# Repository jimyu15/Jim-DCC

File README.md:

## Hardware

Schematics and layouts

Eagle PCB projects

#### Command Center

* DRV8801 enabled 2.8A driving ability with current sensing and protection
* 24-ch occupancy sensing ability
* 8-ch turnout servo control

#### Motor Decoder

* MSP430G2452 16MHz 8-bit MCU
* 24LC02 256Byte EEPROM
* DRV8838 enabled 1.8A driving ability with error protection
* Compatible with KATO DCC ready product

#### Headlight / Taillight Decoder

* MSP430G2452 16MHz 8-bit MCU
* 24LC02 256Byte EEPROM
* 2N7002DW enabled 2-ch 100mA LED driving
* Compatible with KATO DCC ready product

#### Indoor Light Decoder

* MSP430G2452 16MHz 8-bit MCU
* 24LC02 256Byte EEPROM
* 2N7002PW enabled 100mA LED driving

## CV_Writer

A simple tool to write all CVs to decoders.

Energia MSP430 project

## Decoder

Decoder which supports 128 step PWM motor control and general functions

Energia MSP430 project

## DCCpp_UNO

Modified DCC++ command station with occupancy sensing and servo control

Arduino Mega2560 project

Derived from DCC++

https://github.com/DccPlusPlus

## Servo

8-Ch servo control for turnouts

Energia MSP430 project

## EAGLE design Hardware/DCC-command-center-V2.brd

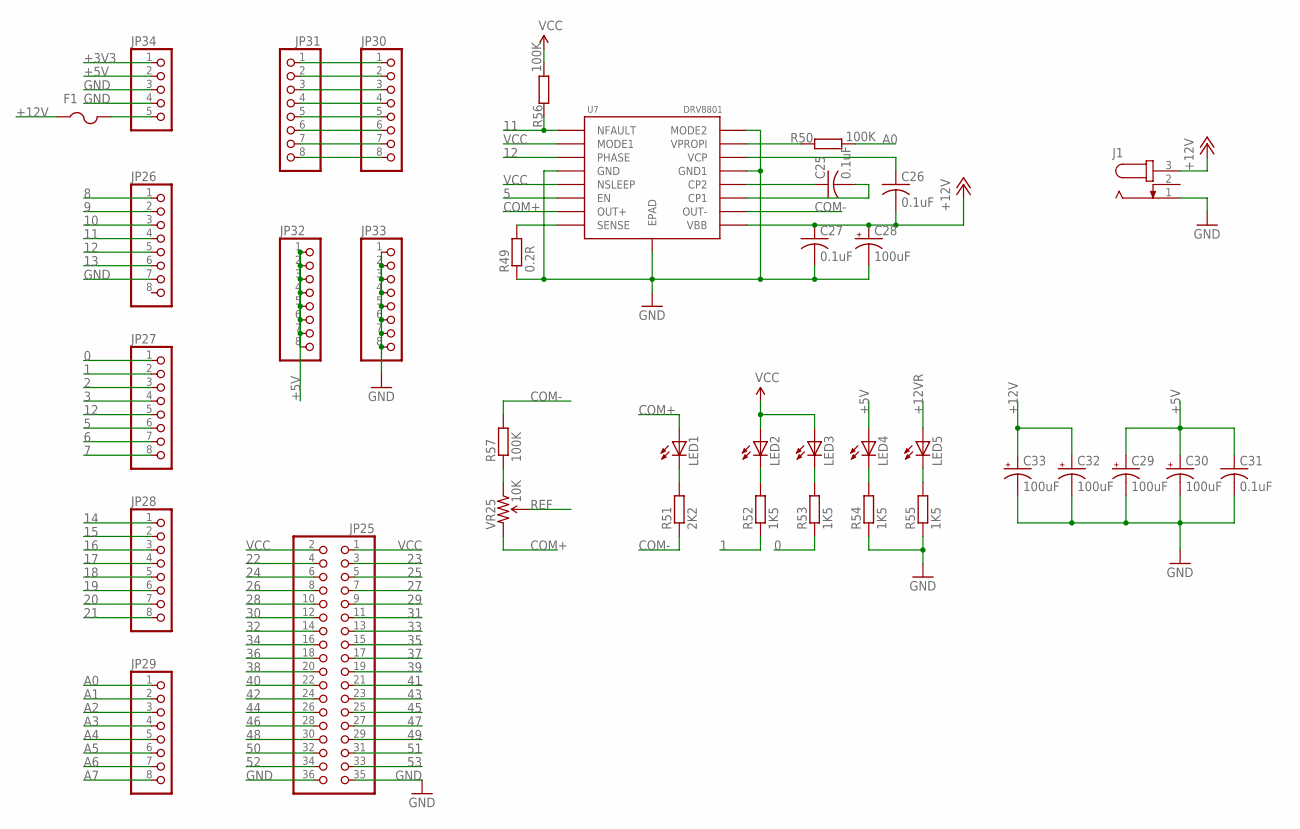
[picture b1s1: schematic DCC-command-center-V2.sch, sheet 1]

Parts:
C25, C26, C27, C31: 0.1uF; C0603
C28, C29, C30, C32, C33: 100uF; 153CLV-0505
F1: PTCFUSE-1812; 1812
J1: RAPC7120; RAPC712
JP25: PINHD-2X18_2.54; 2X18
JP26, JP27, JP28, JP29, JP30, JP31, JP32, JP33: PINHD-1X08_2.54-S; 1X08-S
JP34: PINHD-1X05_2.54-S; 1X05-S
LED1, LED2, LED3, LED4, LED5: LEDCHIP-LED0603; CHIP-LED0603
R49: 0.2R; R2512
R50, R56, R57: 100K; R0603
R51: 2K2; R0603
R52, R53, R54, R55: 1K5; R0603
U7: DRV8801; HTSSOP16
VR25: 10K; TRIMPOT-3MM-2

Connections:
0: JP27.1, R53.1
1: JP27.2, R52.1
2: JP27.3
3: JP27.4
5: JP27.6, U7.P$6 (EN)
6: JP27.7
7: JP27.8
8: JP26.1
9: JP26.2
10: JP26.3
11: JP26.4, R56.2, U7.P$1 (NFAULT)
12: JP26.5, JP27.5, U7.P$3 (PHASE)
13: JP26.6
14: JP28.1
15: JP28.2
16: JP28.3
17: JP28.4
18: JP28.5
19: JP28.6
20: JP28.7
21: JP28.8
22: JP25.4; also elsewhere on the board
23: JP25.3; also elsewhere on the board
24: JP25.6; also elsewhere on the board
25: JP25.5; also elsewhere on the board
26: JP25.8; also elsewhere on the board
27: JP25.7; also elsewhere on the board
28: JP25.10; also elsewhere on the board
29: JP25.9; also elsewhere on the board
30: JP25.12; also elsewhere on the board
31: JP25.11; also elsewhere on the board
32: JP25.14; also elsewhere on the board
33: JP25.13; also elsewhere on the board
34: JP25.16; also elsewhere on the board
35: JP25.15; also elsewhere on the board
36: JP25.18; also elsewhere on the board
37: JP25.17; also elsewhere on the board
38: JP25.20; also elsewhere on the board
39: JP25.19; also elsewhere on the board
40: JP25.22; also elsewhere on the board
41: JP25.21; also elsewhere on the board
42: JP25.24; also elsewhere on the board
43: JP25.23; also elsewhere on the board
44: JP25.26; also elsewhere on the board
45: JP25.25; also elsewhere on the board
46: JP25.28
47: JP25.27
48: JP25.30
49: JP25.29
50: JP25.32
51: JP25.31
52: JP25.34
53: JP25.33
+3V3: JP34.1
+5V: C29.+, C30.+, C31.1, JP32.1, JP32.2, JP32.3, JP32.4, JP32.5, JP32.6, JP32.7, JP32.8, JP34.2, LED4.A
+12V: C26.2, C27.1, C28.+, C32.+, C33.+, F1.1, J1.3, U7.P$9 (VBB)
+12VR: F1.2, JP34.5, LED5.A
A0: JP29.1, R50.1
A1: JP29.2
A2: JP29.3
A3: JP29.4
A4: JP29.5
A5: JP29.6
A6: JP29.7
A7: JP29.8
COM+: LED1.A, U7.P$7 (OUT+), VR25.3 (CW); also elsewhere on the board
COM-: R51.1, R57.2, U7.P$10 (OUT-); also elsewhere on the board
GND: C27.2, C28.-, C29.-, C30.-, C31.2, C32.-, C33.-, J1.1, JP25.35, JP25.36, JP26.7, JP33.1, JP33.2, JP33.3, JP33.4, JP33.5, JP33.6, JP33.7, JP33.8, JP34.3, JP34.4, R49.1, R54.1, R55.1, U7.P$4 (GND), U7.P$13 (GND1), U7.P$16 (MODE2), U7.P$17 (EPAD); also elsewhere on the board
unnamed: JP30.1, JP31.1
unnamed: JP30.2, JP31.2
unnamed: JP30.3, JP31.3
unnamed: JP30.4, JP31.4
unnamed: JP30.5, JP31.5
unnamed: JP30.6, JP31.6
unnamed: JP30.7, JP31.7
unnamed: JP30.8, JP31.8
unnamed: R49.2, U7.P$8 (SENSE)
unnamed: C25.1, U7.P$12 (CP2)
unnamed: C25.2, U7.P$11 (CP1)
unnamed: C26.1, U7.P$14 (VCP)
unnamed: R57.1, VR25.1 (CCW)
unnamed: R50.2, U7.P$15 (VPROPI)
unnamed: LED1.C, R51.2
unnamed: LED2.C, R52.2
unnamed: LED3.C, R53.2
unnamed: LED4.C, R54.2
unnamed: LED5.C, R55.2
REF: VR25.2 (WIPER); also elsewhere on the board
VCC: JP25.1, JP25.2, LED2.A, LED3.A, R56.1, U7.P$2 (MODE1), U7.P$5 (NSLEEP); also elsewhere on the board

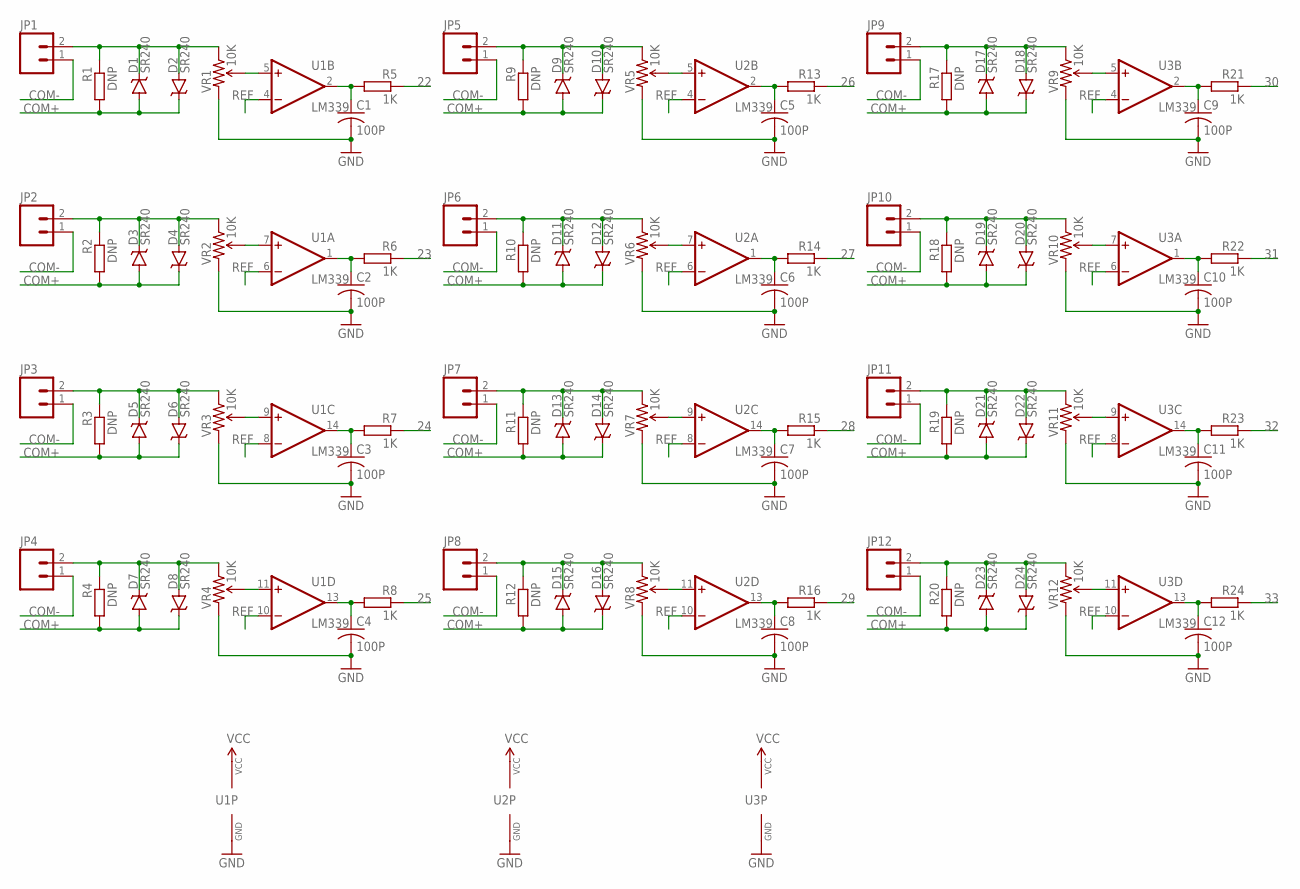
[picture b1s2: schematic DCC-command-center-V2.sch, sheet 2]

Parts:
C1, C2, C3, C4, C5, C6, C7, C8, C9, C10, C11, C12: 100P; C0603
D1, D2, D3, D4, D5, D6, D7, D8, D9, D10, D11, D12, D13, D14, D15, D16, D17, D18, D19, D20, D21, D22, D23, D24: SR240; SMA-DIODE
JP1, JP2, JP3, JP4, JP5, JP6, JP7, JP8, JP9, JP10, JP11, JP12: M02POGO_PIN_HOLES_ONLY; 1X02_PP_HOLES_ONLY
R1, R2, R3, R4, R9, R10, R11, R12, R17, R18, R19, R20: DNP; R0603
R5, R6, R7, R8, R13, R14, R15, R16, R21, R22, R23, R24: 1K; R0603
U1, U2, U3: LM339; TSSOP-14
VR1, VR2, VR3, VR4, VR5, VR6, VR7, VR8, VR9, VR10, VR11, VR12: 10K; TRIMPOT-3MM-2

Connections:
22: R5.1; also elsewhere on the board
23: R6.1; also elsewhere on the board
24: R7.1; also elsewhere on the board
25: R8.1; also elsewhere on the board
26: R13.1; also elsewhere on the board
27: R14.1; also elsewhere on the board
28: R15.1; also elsewhere on the board
29: R16.1; also elsewhere on the board
30: R21.1; also elsewhere on the board
31: R22.1; also elsewhere on the board
32: R23.1; also elsewhere on the board
33: R24.1; also elsewhere on the board
COM+: D1.A, D2.C, D3.A, D4.C, D5.A, D6.C, D7.A, D8.C, D9.A, D10.C, D11.A, D12.C, D13.A, D14.C, D15.A, D16.C, D17.A, D18.C, D19.A, D20.C, D21.A, D22.C, D23.A, D24.C, R1.2, R2.2, R3.2, R4.2, R9.2, R10.2, R11.2, R12.2, R17.2, R18.2, R19.2, R20.2; also elsewhere on the board
COM-: JP1.1, JP2.1, JP3.1, JP4.1, JP5.1, JP6.1, JP7.1, JP8.1, JP9.1, JP10.1, JP11.1, JP12.1; also elsewhere on the board
GND: C1.2, C2.2, C3.2, C4.2, C5.2, C6.2, C7.2, C8.2, C9.2, C10.2, C11.2, C12.2, U1.12 (GND), U2.12 (GND), U3.12 (GND), VR1.3 (CW), VR2.3 (CW), VR3.3 (CW), VR4.3 (CW), VR5.3 (CW), VR6.3 (CW), VR7.3 (CW), VR8.3 (CW), VR9.3 (CW), VR10.3 (CW), VR11.3 (CW), VR12.3 (CW); also elsewhere on the board
JP1: D1.C, D2.A, JP1.2, R1.1, VR1.1 (CCW)
JP2: D3.C, D4.A, JP2.2, R2.1, VR2.1 (CCW)
JP3: D5.C, D6.A, JP3.2, R3.1, VR3.1 (CCW)
JP4: D7.C, D8.A, JP4.2, R4.1, VR4.1 (CCW)
JP5: D9.C, D10.A, JP5.2, R9.1, VR5.1 (CCW)
JP6: D11.C, D12.A, JP6.2, R10.1, VR6.1 (CCW)
JP7: D13.C, D14.A, JP7.2, R11.1, VR7.1 (CCW)
JP8: D15.C, D16.A, JP8.2, R12.1, VR8.1 (CCW)
JP9: D17.C, D18.A, JP9.2, R17.1, VR9.1 (CCW)
JP10: D19.C, D20.A, JP10.2, R18.1, VR10.1 (CCW)
JP11: D21.C, D22.A, JP11.2, R19.1, VR11.1 (CCW)
JP12: D23.C, D24.A, JP12.2, R20.1, VR12.1 (CCW)
OP1: C1.1, R5.2, U1.2 (OUT)
OP2: C2.1, R6.2, U1.1 (OUT)
OP3: C3.1, R7.2, U1.14 (OUT)
OP4: C4.1, R8.2, U1.13 (OUT)
OP5: C5.1, R13.2, U2.2 (OUT)
OP6: C6.1, R14.2, U2.1 (OUT)
OP7: C7.1, R15.2, U2.14 (OUT)
OP8: C8.1, R16.2, U2.13 (OUT)
OP9: C9.1, R21.2, U3.2 (OUT)
OP10: C10.1, R22.2, U3.1 (OUT)
OP11: C11.1, R23.2, U3.14 (OUT)
OP12: C12.1, R24.2, U3.13 (OUT)
REF: U1.4 (-IN), U1.6 (-IN), U1.8 (-IN), U1.10 (-IN), U2.4 (-IN), U2.6 (-IN), U2.8 (-IN), U2.10 (-IN), U3.4 (-IN), U3.6 (-IN), U3.8 (-IN), U3.10 (-IN); also elsewhere on the board
VCC: U1.3 (VCC), U2.3 (VCC), U3.3 (VCC); also elsewhere on the board
VR1: U1.5 (+IN), VR1.2 (WIPER)
VR2: U1.7 (+IN), VR2.2 (WIPER)
VR3: U1.9 (+IN), VR3.2 (WIPER)
VR4: U1.11 (+IN), VR4.2 (WIPER)
VR5: U2.5 (+IN), VR5.2 (WIPER)
VR6: U2.7 (+IN), VR6.2 (WIPER)
VR7: U2.9 (+IN), VR7.2 (WIPER)
VR8: U2.11 (+IN), VR8.2 (WIPER)
VR9: U3.5 (+IN), VR9.2 (WIPER)
VR10: U3.7 (+IN), VR10.2 (WIPER)
VR11: U3.9 (+IN), VR11.2 (WIPER)
VR12: U3.11 (+IN), VR12.2 (WIPER)

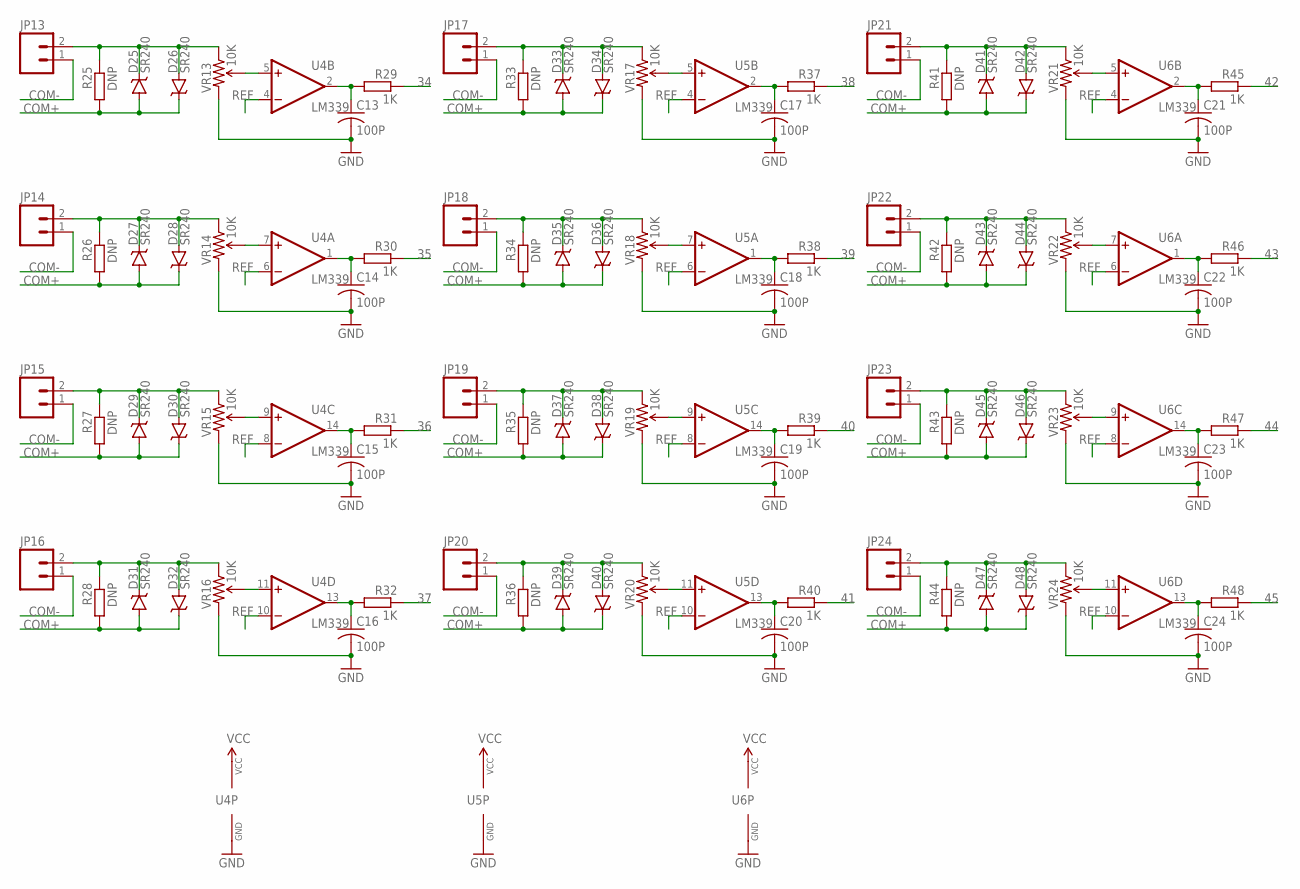
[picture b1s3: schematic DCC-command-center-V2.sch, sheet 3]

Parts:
C13, C14, C15, C16, C17, C18, C19, C20, C21, C22, C23, C24: 100P; C0603
D25, D26, D27, D28, D29, D30, D31, D32, D33, D34, D35, D36, D37, D38, D39, D40, D41, D42, D43, D44, D45, D46, D47, D48: SR240; SMA-DIODE
JP13, JP14, JP15, JP16, JP17, JP18, JP19, JP20, JP21, JP22, JP23, JP24: M02POGO_PIN_HOLES_ONLY; 1X02_PP_HOLES_ONLY
R25, R26, R27, R28, R33, R34, R35, R36, R41, R42, R43, R44: DNP; R0603
R29, R30, R31, R32, R37, R38, R39, R40, R45, R46, R47, R48: 1K; R0603
U4, U5, U6: LM339; TSSOP-14
VR13, VR14, VR15, VR16, VR17, VR18, VR19, VR20, VR21, VR22, VR23, VR24: 10K; TRIMPOT-3MM-2

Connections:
34: R29.1; also elsewhere on the board
35: R30.1; also elsewhere on the board
36: R31.1; also elsewhere on the board
37: R32.1; also elsewhere on the board
38: R37.1; also elsewhere on the board
39: R38.1; also elsewhere on the board
40: R39.1; also elsewhere on the board
41: R40.1; also elsewhere on the board
42: R45.1; also elsewhere on the board
43: R46.1; also elsewhere on the board
44: R47.1; also elsewhere on the board
45: R48.1; also elsewhere on the board
COM+: D25.A, D26.C, D27.A, D28.C, D29.A, D30.C, D31.A, D32.C, D33.A, D34.C, D35.A, D36.C, D37.A, D38.C, D39.A, D40.C, D41.A, D42.C, D43.A, D44.C, D45.A, D46.C, D47.A, D48.C, R25.2, R26.2, R27.2, R28.2, R33.2, R34.2, R35.2, R36.2, R41.2, R42.2, R43.2, R44.2; also elsewhere on the board
COM-: JP13.1, JP14.1, JP15.1, JP16.1, JP17.1, JP18.1, JP19.1, JP20.1, JP21.1, JP22.1, JP23.1, JP24.1; also elsewhere on the board
GND: C13.2, C14.2, C15.2, C16.2, C17.2, C18.2, C19.2, C20.2, C21.2, C22.2, C23.2, C24.2, U4.12 (GND), U5.12 (GND), U6.12 (GND), VR13.3 (CW), VR14.3 (CW), VR15.3 (CW), VR16.3 (CW), VR17.3 (CW), VR18.3 (CW), VR19.3 (CW), VR20.3 (CW), VR21.3 (CW), VR22.3 (CW), VR23.3 (CW), VR24.3 (CW); also elsewhere on the board
JP13: D25.C, D26.A, JP13.2, R25.1, VR13.1 (CCW)
JP14: D27.C, D28.A, JP14.2, R26.1, VR14.1 (CCW)
JP15: D29.C, D30.A, JP15.2, R27.1, VR15.1 (CCW)
JP16: D31.C, D32.A, JP16.2, R28.1, VR16.1 (CCW)
JP17: D33.C, D34.A, JP17.2, R33.1, VR17.1 (CCW)
JP18: D35.C, D36.A, JP18.2, R34.1, VR18.1 (CCW)
JP19: D37.C, D38.A, JP19.2, R35.1, VR19.1 (CCW)
JP20: D39.C, D40.A, JP20.2, R36.1, VR20.1 (CCW)
JP21: D41.C, D42.A, JP21.2, R41.1, VR21.1 (CCW)
JP22: D43.C, D44.A, JP22.2, R42.1, VR22.1 (CCW)
JP23: D45.C, D46.A, JP23.2, R43.1, VR23.1 (CCW)
JP24: D47.C, D48.A, JP24.2, R44.1, VR24.1 (CCW)
OP13: C13.1, R29.2, U4.2 (OUT)
OP14: C14.1, R30.2, U4.1 (OUT)
OP15: C15.1, R31.2, U4.14 (OUT)
OP16: C16.1, R32.2, U4.13 (OUT)
OP17: C17.1, R37.2, U5.2 (OUT)
OP18: C18.1, R38.2, U5.1 (OUT)
OP19: C19.1, R39.2, U5.14 (OUT)
OP20: C20.1, R40.2, U5.13 (OUT)
OP21: C21.1, R45.2, U6.2 (OUT)
OP22: C22.1, R46.2, U6.1 (OUT)
OP23: C23.1, R47.2, U6.14 (OUT)
OP24: C24.1, R48.2, U6.13 (OUT)
REF: U4.4 (-IN), U4.6 (-IN), U4.8 (-IN), U4.10 (-IN), U5.4 (-IN), U5.6 (-IN), U5.8 (-IN), U5.10 (-IN), U6.4 (-IN), U6.6 (-IN), U6.8 (-IN), U6.10 (-IN); also elsewhere on the board
VCC: U4.3 (VCC), U5.3 (VCC), U6.3 (VCC); also elsewhere on the board
VR13: U4.5 (+IN), VR13.2 (WIPER)
VR14: U4.7 (+IN), VR14.2 (WIPER)
VR15: U4.9 (+IN), VR15.2 (WIPER)
VR16: U4.11 (+IN), VR16.2 (WIPER)
VR17: U5.5 (+IN), VR17.2 (WIPER)
VR18: U5.7 (+IN), VR18.2 (WIPER)
VR19: U5.9 (+IN), VR19.2 (WIPER)
VR20: U5.11 (+IN), VR20.2 (WIPER)
VR21: U6.5 (+IN), VR21.2 (WIPER)
VR22: U6.7 (+IN), VR22.2 (WIPER)
VR23: U6.9 (+IN), VR23.2 (WIPER)
VR24: U6.11 (+IN), VR24.2 (WIPER)

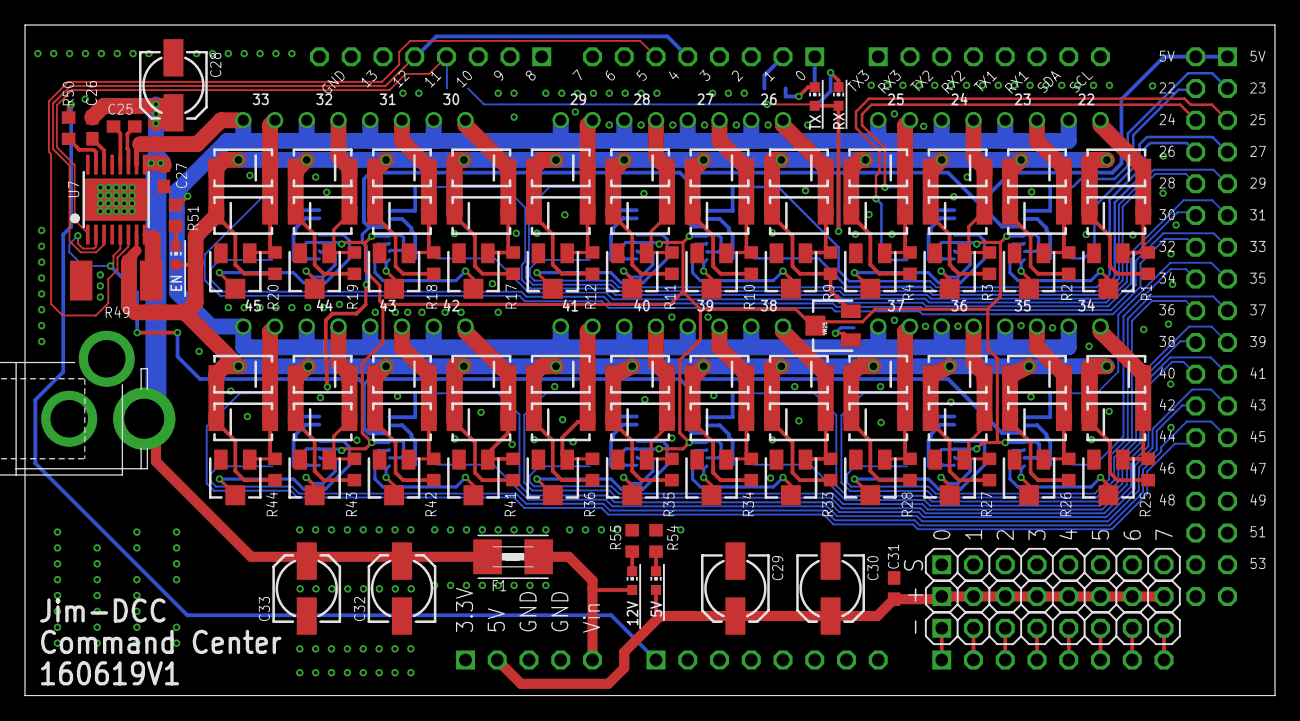
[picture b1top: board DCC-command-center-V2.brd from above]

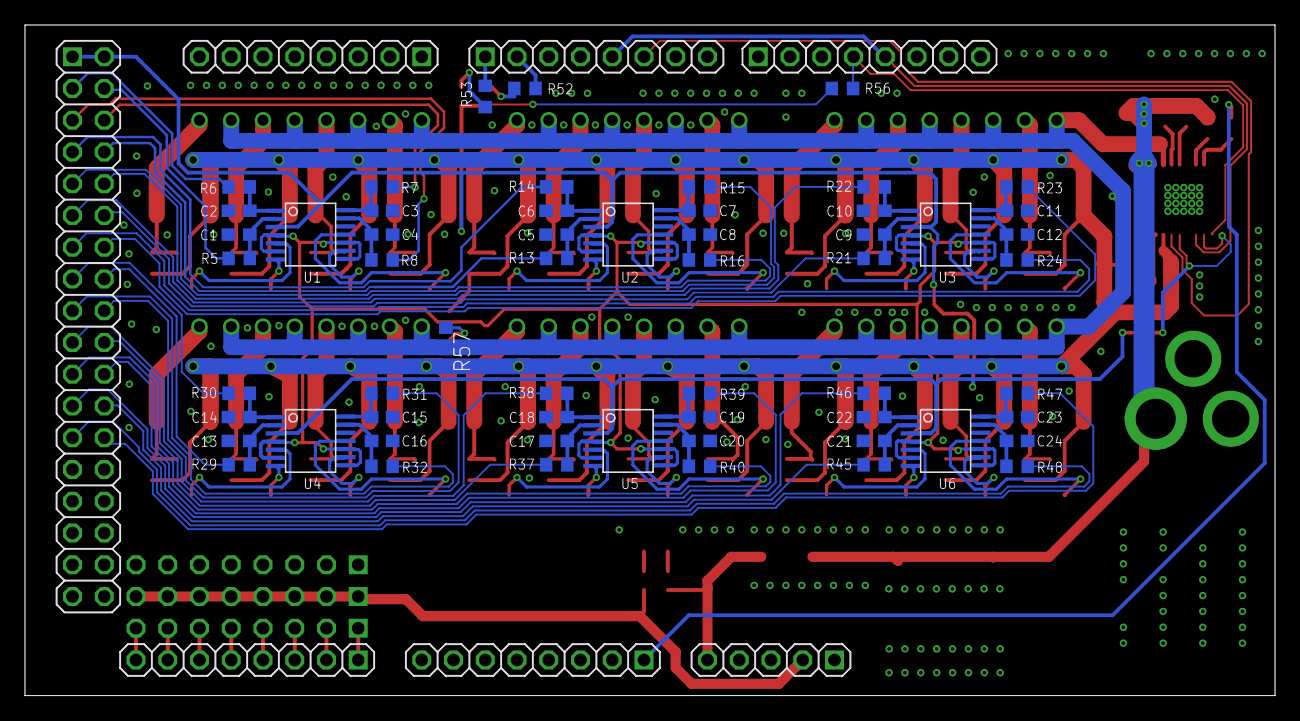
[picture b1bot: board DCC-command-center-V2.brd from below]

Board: 2 copper layers, 100.0 x 53.6 mm, 211 parts (66 on the bottom side), 129 nets.

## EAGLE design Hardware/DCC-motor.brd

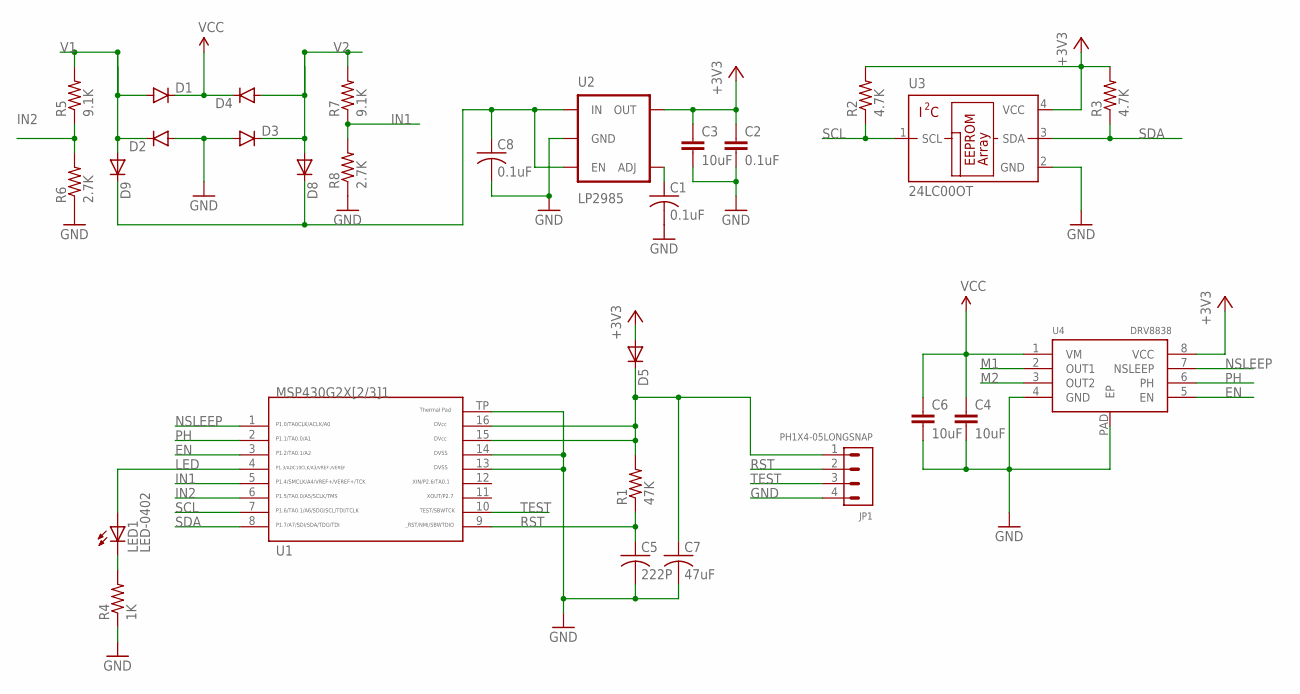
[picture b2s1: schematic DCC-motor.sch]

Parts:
C1, C8: 0.1uF; C0402
C2: 0.1uF; 0603-CAP
C3, C4, C6: 10uF; 0603-CAP
C5: 222P; C0402
C7: 47uF; C0402
D1, D2, D3, D4: DIODESOD123; SOD-123
D5, D8, D9: DIODE-SOD523; SOD523
JP1: PH1X4-05LONGSNAP; PHLS005-1-4
LED1: LED-0402; 0402-LED
R1: 47K; R0402
R2, R3: 4.7K; R0402
R4: 1K; R0402
R5, R7: 9.1K; R0402
R6, R8: 2.7K; R0402
U1: G2X[2/3]1---RSA16; RSA16
U2: LP2985; SOT23-5
U3: 24LC00OT; SOT23-5L
U4: DRV8838; WSON-8-PAD

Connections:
+3V3: C2.1, C3.1, D5.A, R2.2, R3.2, U2.5 (OUT), U3.4 (VCC), U4.8 (VCC)
EN: U1.3, U4.5 (EN)
GND: C1.2, C2.2, C3.2, C4.2, C5.2, C6.2, C7.2, C8.2, D2.A, D3.A, JP1.4, R4.1, R6.1, R8.1, U1.13, U1.14, U1.TP, U2.2 (GND), U3.2 (GND), U4.4 (GND), U4.PAD (EP)
IN1: R7.1, R8.2, U1.5
IN2: R5.1, R6.2, U1.6
LED: LED1.A, U1.4
M1: U4.2 (OUT1)
M2: U4.3 (OUT2)
unnamed: C1.1, U2.4 (ADJ)
unnamed: C8.1, D8.C, D9.C, U2.1 (IN), U2.3 (EN)
unnamed: LED1.C, R4.2
unnamed: C7.1, D5.C, JP1.1, R1.2, U1.15, U1.16
NSLEEP: U1.1, U4.7 (NSLEEP)
PH: U1.2, U4.6 (PH)
RST: C5.1, JP1.2, R1.1, U1.9
SCL: R2.1, U1.7, U3.1 (SCL)
SDA: R3.1, U1.8, U3.3 (SDA)
TEST: JP1.3, U1.10
V1: D1.A, D2.C, D9.A, R5.2
V2: D3.C, D4.A, D8.A, R7.2
VCC: C4.1, C6.1, D1.C, D4.C, U4.1 (VM)

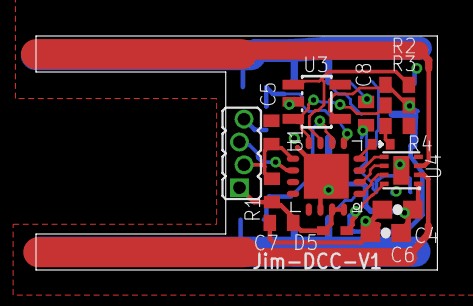
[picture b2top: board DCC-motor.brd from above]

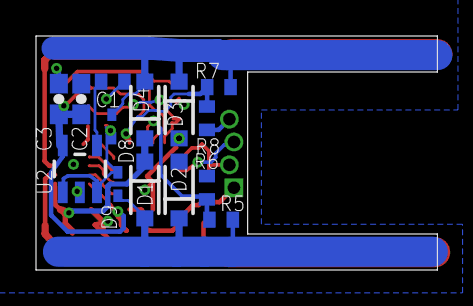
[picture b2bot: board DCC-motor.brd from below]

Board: 2 copper layers, 22.3 x 13.0 mm, 29 parts (14 on the bottom side), 19 nets.

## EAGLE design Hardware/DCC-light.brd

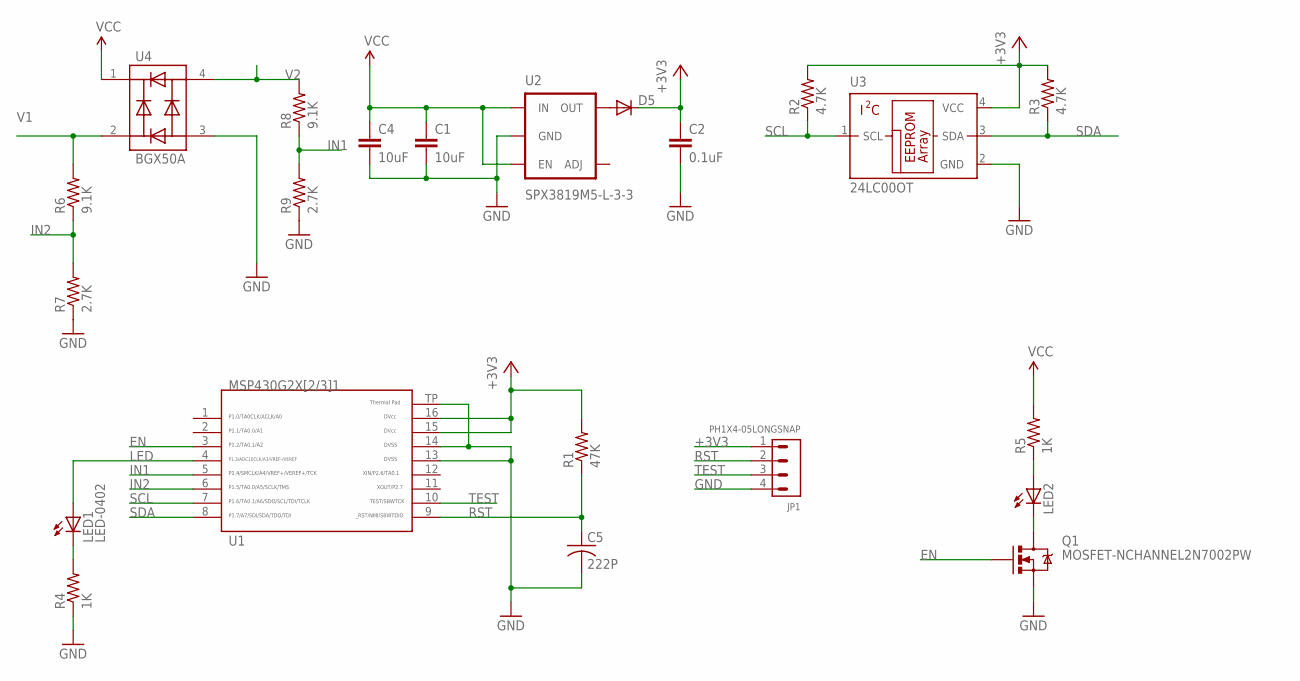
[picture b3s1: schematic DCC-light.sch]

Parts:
C1: 10uF; 0402-CAP
C2: 0.1uF; 0603-CAP
C4: 10uF; 0603-CAP
C5: 222P; C0402
D5: DIODE-SOD523; SOD523
JP1: PH1X4-05LONGSNAP; PHLS005-1-4
LED1: LED-0402; 0402-LED
LED2: LEDSMT1206; 1206
Q1: MOSFET-NCHANNEL2N7002PW; SOT323
R1: 47K; R0402
R2, R3: 4.7K; R0402
R4: 1K; R0402
R5: 1K; R0603
R6, R8: 9.1K; R0402
R7, R9: 2.7K; R0402
U1: G2X[2/3]1---RSA16; RSA16
U2: SPX3819M5-L-3-3; SOT23-5
U3: 24LC00OT; SOT23-5L
U4: BGX50A; SOT143

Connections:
+3V3: C2.1, D5.C, JP1.1, R1.2, R2.2, R3.2, U1.15, U1.16, U3.4 (VCC)
EN: Q1.1 (G), U1.3
GND: C1.2, C2.2, C4.2, C5.2, JP1.4, Q1.2 (S), R4.1, R7.1, R9.1, U1.13, U1.14, U1.TP, U2.2 (GND), U3.2 (GND), U4.3
IN1: R8.1, R9.2, U1.5
IN2: R6.1, R7.2, U1.6
LED: LED1.A, U1.4
unnamed: LED2.C, Q1.3 (D)
unnamed: LED2.A, R5.1
unnamed: LED1.C, R4.2
unnamed: D5.A, U2.5 (OUT)
RST: C5.1, JP1.2, R1.1, U1.9
SCL: R2.1, U1.7, U3.1 (SCL)
SDA: R3.1, U1.8, U3.3 (SDA)
TEST: JP1.3, U1.10
V1: R6.2, U4.2
V2: R8.2, U4.4
VCC: C1.1, C4.1, R5.2, U2.1 (IN), U2.3 (EN), U4.1

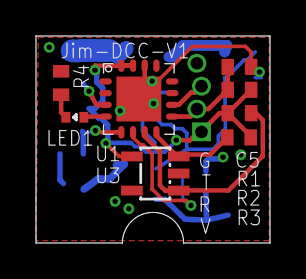
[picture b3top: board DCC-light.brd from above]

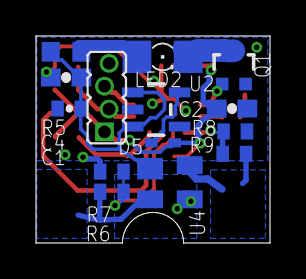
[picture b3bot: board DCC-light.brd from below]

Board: 2 copper layers, 13.0 x 11.5 mm, 22 parts (14 on the bottom side), 17 nets.

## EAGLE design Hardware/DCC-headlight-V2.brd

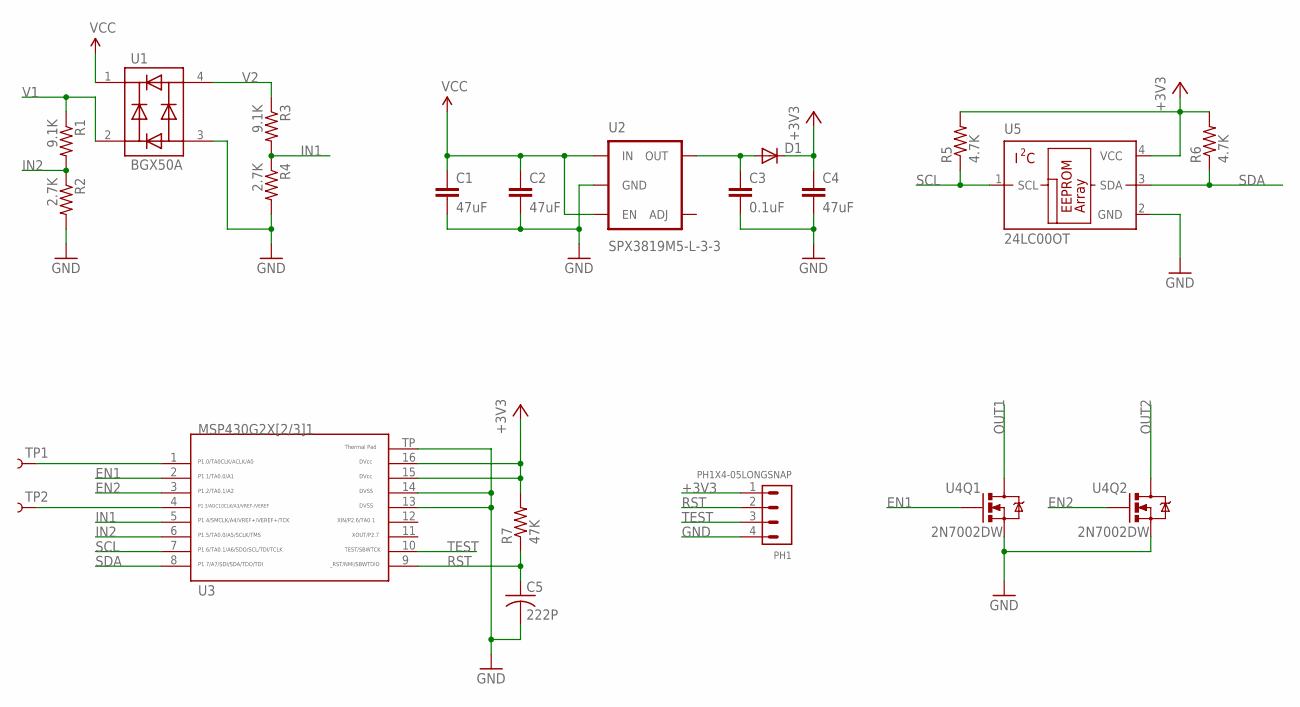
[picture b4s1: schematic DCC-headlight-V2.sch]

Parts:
C1, C2, C4: 47uF; 0402-CAP
C3: 0.1uF; 0402-CAP
C5: 222P; C0402
D1: DIODE-SOD523; SOD523
PH1: PH1X4-05LONGSNAP; PHLS005-1-4
R1, R3: 9.1K; R0402
R2, R4: 2.7K; R0402
R5, R6: 4.7K; R0402
R7: 47K; R0402
TP1, TP2: TEST-POINT3; PAD.03X.03
U1: BGX50A; SOT143
U2: SPX3819M5-L-3-3; SOT23-5
U3: G2X[2/3]1---RSA16; RSA16
U4: 2N7002DW; SOT363
U5: 24LC00OT; SOT23-5L

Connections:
+3V3: C4.1, D1.C, PH1.1, R5.2, R6.2, R7.2, U3.15, U3.16, U5.4 (VCC)
EN1: U3.2, U4.2 (G)
EN2: U3.3, U4.5 (G)
GND: C1.2, C2.2, C3.2, C4.2, C5.2, PH1.4, R2.2, R4.2, U1.3, U2.2 (GND), U3.13, U3.14, U3.TP, U4.1 (S), U4.4 (S), U5.2 (GND)
IN1: R3.2, R4.1, U3.5
IN2: R1.2, R2.1, U3.6
unnamed: C3.1, D1.A, U2.5 (OUT)
OUT1: U4.6 (D)
OUT2: U4.3 (D)
RST: C5.1, PH1.2, R7.1, U3.9
SCL: R5.1, U3.7, U5.1 (SCL)
SDA: R6.1, U3.8, U5.3 (SDA)
TEST: PH1.3, U3.10
TP1: TP1.P$1, U3.1
TP2: TP2.P$1, U3.4
V1: R1.1, U1.2
V2: R3.1, U1.4
VCC: C1.1, C2.1, U1.1, U2.1 (IN), U2.3 (EN)

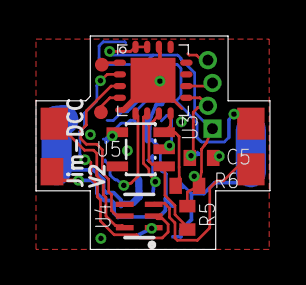
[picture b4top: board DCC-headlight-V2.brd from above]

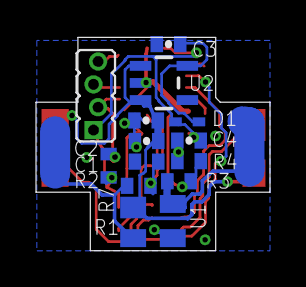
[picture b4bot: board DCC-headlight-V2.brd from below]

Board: 2 copper layers, 13.0 x 11.9 mm, 21 parts (13 on the bottom side), 16 nets.

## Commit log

2016-05-30 Create Repository
2016-06-02 6/2 checkpoint
2016-06-02 Debugging
2016-06-02 Inverting Logic
2016-06-04 Add control function
2016-06-05 Create DCCpp
2016-06-05 Servo turnout function
2016-06-08 Improve Motor Control
2016-06-09 Add decoder debug communication
2016-06-09 Improve packet reading and motor control
2016-06-09 Create CV writer
2016-06-09 Upload hardware design files
2016-06-09 Comparator sensor input and servo turnout supported
2016-06-18 Flashing LED after writing EEPROM
2016-06-18 Add testing function
2016-06-25 Sensor bug fixed
2016-06-26 Update hardware design
2016-06-26 Command and storage for servo position configuration
2016-06-26 Update component values
2016-07-08 Eliminate servo audible noise
2016-07-14 Remove EEPROM; Add ACLK support;

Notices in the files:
parts and their libraries:
SparkFun-DiscreteSemi: Licensing: Creative Commons ShareAlike 4.0 International - https://creativecommons.org/licenses/by-sa/4.0
microbuilder: This work is placed in the public domain, and may be freely used for commercial and non-commercial work with the following conditions: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
